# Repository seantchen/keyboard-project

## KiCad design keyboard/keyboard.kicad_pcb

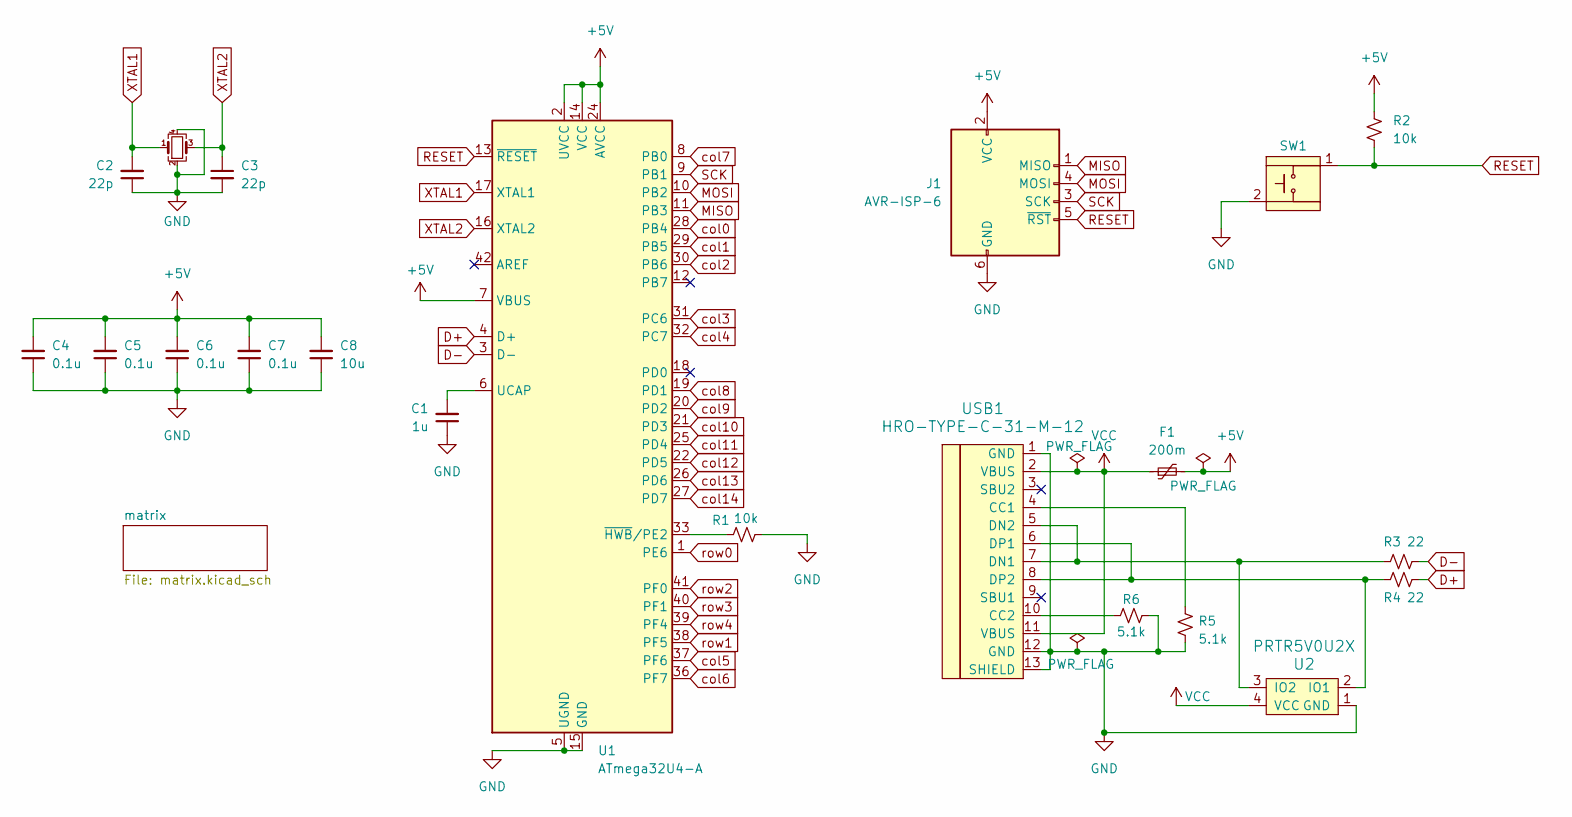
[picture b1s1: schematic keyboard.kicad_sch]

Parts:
C1: 1u; C_0805_2012Metric_Pad1.18x1.45mm_HandSolder
C2, C3: 22p; C_0805_2012Metric_Pad1.18x1.45mm_HandSolder
C4, C5, C6, C7: 0.1u; C_0805_2012Metric_Pad1.18x1.45mm_HandSolder
C8: 10u; C_0805_2012Metric_Pad1.18x1.45mm_HandSolder
F1: 200m; Fuse_1206_3216Metric_Pad1.42x1.75mm_HandSolder
J1: AVR-ISP-6; Reset_Pretty-Mask
R1, R2: 10k; R_0805_2012Metric_Pad1.20x1.40mm_HandSolder
R3, R4: 22; R_0805_2012Metric_Pad1.20x1.40mm_HandSolder
R5, R6: 5.1k; R_0805_2012Metric_Pad1.20x1.40mm_HandSolder
SW1: SW_SPST_SKQG_WithStem
U1: ATmega32U4-A; TQFP-44_10x10mm_P0.8mm
U2: PRTR5V0U2X; SOT143B
USB1: HRO-TYPE-C-31-M-12; HRO-TYPE-C-31-M-12-HandSoldering
Y1: Crystal_GND24_Small; Crystal_SMD_3225-4Pin_3.2x2.5mm_HandSoldering

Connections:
+5V: C4.2, C5.2, C6.2, C7.2, C8.2, F1.2, J1.2 (VCC), R2.1, U1.2 (UVCC), U1.7 (VBUS), U1.14 (VCC), U1.24 (AVCC), U1.34 (VCC), U1.44 (AVCC)
D+: R4.2, U1.4 (D+)
D-: R3.2, U1.3 (D-)
GND: C1.1, C2.1, C3.2, C4.1, C5.1, C6.1, C7.1, C8.1, J1.6 (GND), R1.2, R5.2, R6.2, SW1.2, U1.5 (UGND), U1.15 (GND), U1.23 (GND), U1.35 (GND), U1.43 (GND), U2.1 (GND), USB1.1 (GND), USB1.12 (GND), USB1.13 (SHIELD), Y1.2, Y1.4
MISO: J1.1 (MISO), U1.11 (PB3)
MOSI: J1.4 (MOSI), U1.10 (PB2)
unnamed: C1.2, U1.6 (UCAP)
unnamed: R1.1, U1.33 (~HWB/PE2)
unnamed: R4.1, U2.2 (IO1), USB1.6 (DP1), USB1.8 (DP2)
unnamed: R3.1, U2.3 (IO2), USB1.5 (DN2), USB1.7 (DN1)
unnamed: R5.1, USB1.4 (CC1)
unnamed: R6.1, USB1.10 (CC2)
RESET: J1.5 (~RST), R2.2, SW1.1, U1.13 (~RESET)
SCK: J1.3 (SCK), U1.9 (PB1)
VCC: F1.1, U2.4 (VCC), USB1.2 (VBUS), USB1.11 (VBUS)
XTAL1: C2.2, U1.17 (XTAL1), Y1.1
XTAL2: C3.1, U1.16 (XTAL2), Y1.3
col0: U1.28 (PB4); also elsewhere on the board
col1: U1.29 (PB5); also elsewhere on the board
col2: U1.30 (PB6); also elsewhere on the board
col3: U1.31 (PC6); also elsewhere on the board
col4: U1.32 (PC7); also elsewhere on the board
col5: U1.37 (PF6); also elsewhere on the board
col6: U1.36 (PF7); also elsewhere on the board
col7: U1.8 (PB0); also elsewhere on the board
col8: U1.19 (PD1); also elsewhere on the board
col9: U1.20 (PD2); also elsewhere on the board
col10: U1.21 (PD3); also elsewhere on the board
col11: U1.25 (PD4); also elsewhere on the board
col12: U1.22 (PD5); also elsewhere on the board
col13: U1.26 (PD6); also elsewhere on the board
col14: U1.27 (PD7); also elsewhere on the board
row0: U1.1 (PE6); also elsewhere on the board
row1: U1.38 (PF5); also elsewhere on the board
row2: U1.41 (PF0); also elsewhere on the board
row3: U1.40 (PF1); also elsewhere on the board
row4: U1.39 (PF4); also elsewhere on the board

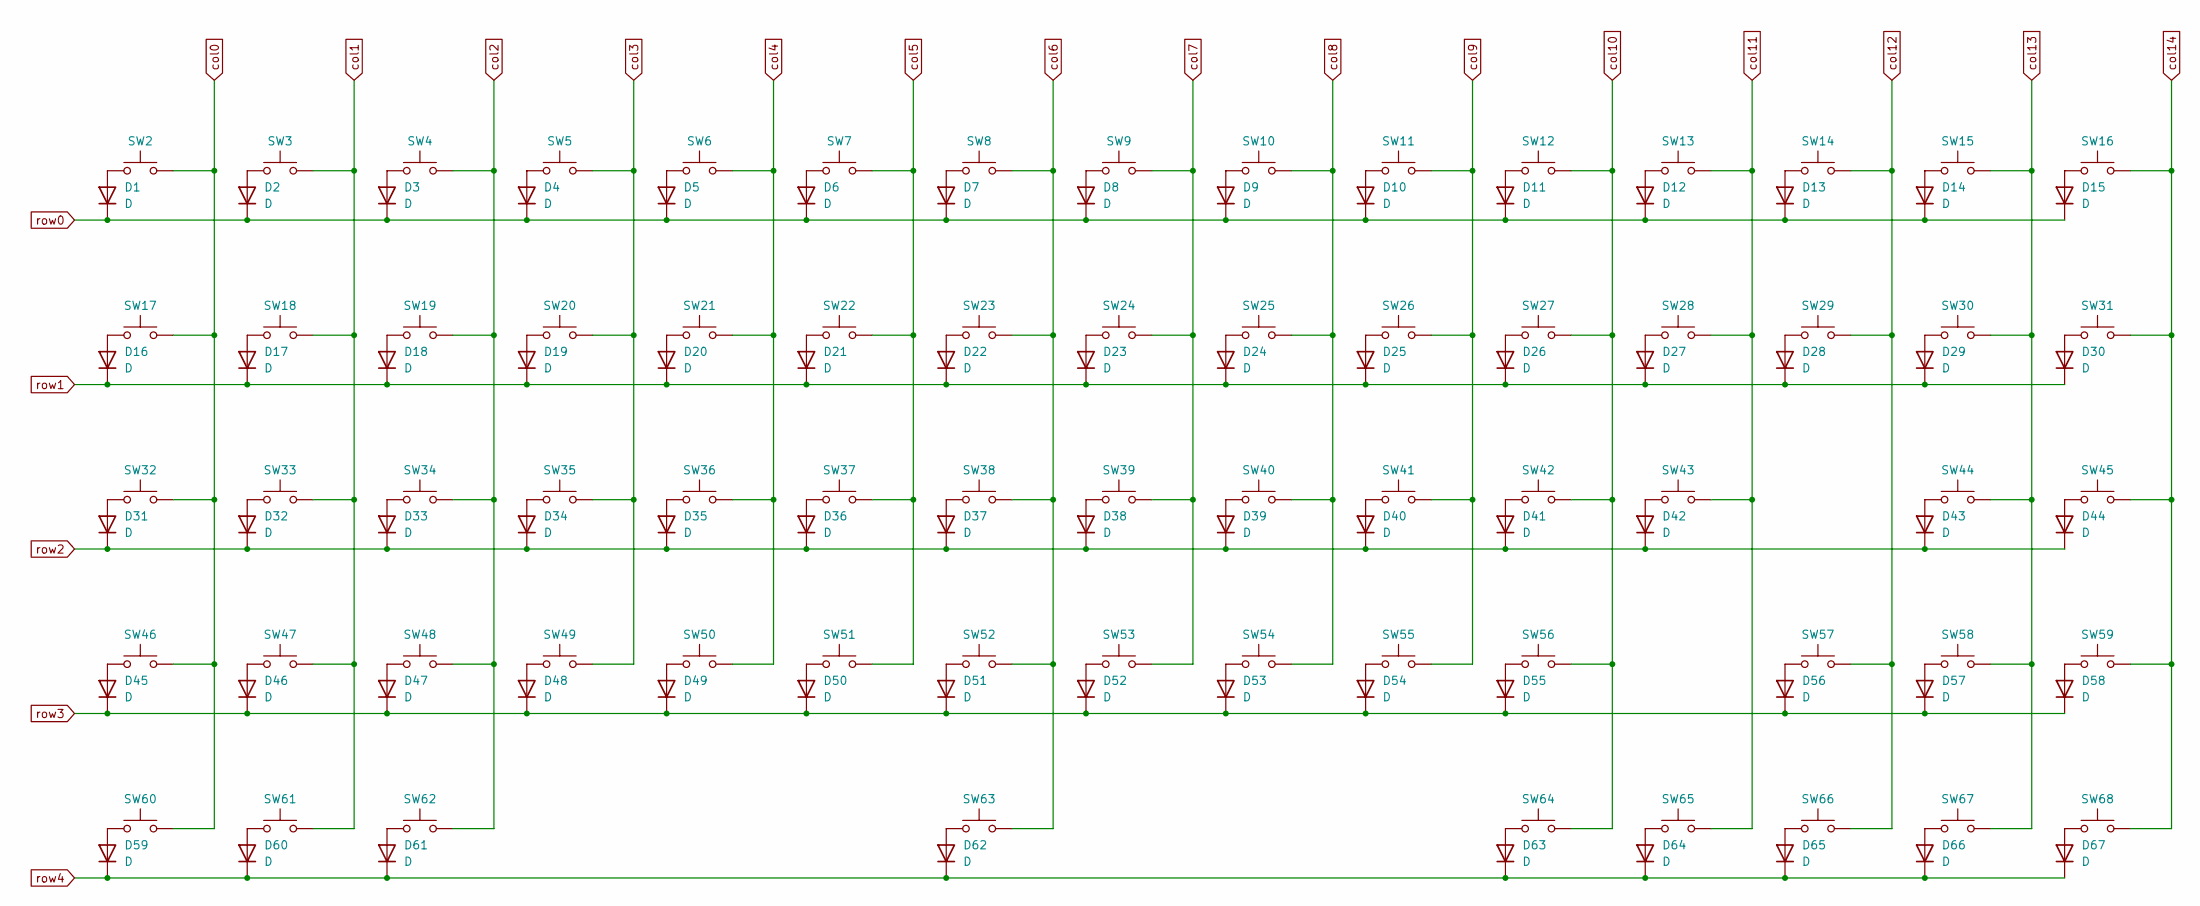
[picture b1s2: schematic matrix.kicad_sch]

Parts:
D1, D2, D3, D4, D5, D6, D7, D8, D9, D10, D11, D12, D13, D14, D15, D16, D17, D18, D19, D20, D21, D22, D23, D24, D25, D26, D27, D28, D29, D30, D31, D32, D33, D34, D35, D36, D37, D38, D39, D40, D41, D42, D43, D44, D45, D46, D47, D48, D49, D50, D51, D52, D53, D54, D55, D56, D57, D58, D59, D60, D61, D62, D63, D64, D65, D66, D67: D; D_SOD-123
SW2: ESC; MXOnly-1U-NoLED
SW3: 1; MXOnly-1U-NoLED
SW4: 2; MXOnly-1U-NoLED
SW5: 3; MXOnly-1U-NoLED
SW6: 4; MXOnly-1U-NoLED
SW7: 5; MXOnly-1U-NoLED
SW8: 6; MXOnly-1U-NoLED
SW9: 7; MXOnly-1U-NoLED
SW10: 8; MXOnly-1U-NoLED
SW11: 9; MXOnly-1U-NoLED
SW12: 0; MXOnly-1U-NoLED
SW13: -_; MXOnly-1U-NoLED
SW14: +=; MXOnly-1U-NoLED
SW15: BSPC; MXOnly-2U-NoLED
SW16: DEL; MXOnly-1U-NoLED
SW17: TAB; MXOnly-1.5U-NoLED
SW18: Q; MXOnly-1U-NoLED
SW19: W; MXOnly-1U-NoLED
SW20: E; MXOnly-1U-NoLED
SW21: R; MXOnly-1U-NoLED
SW22: T; MXOnly-1U-NoLED
SW23: Y; MXOnly-1U-NoLED
SW24: U; MXOnly-1U-NoLED
SW25: I; MXOnly-1U-NoLED
SW26: O; MXOnly-1U-NoLED
SW27: P; MXOnly-1U-NoLED
SW28: {[; MXOnly-1U-NoLED
SW29: }]; MXOnly-1U-NoLED
SW30: |\; MXOnly-1.5U-NoLED
SW31: PGUP; MXOnly-1U-NoLED
SW32: CAPS; MXOnly-1.75U-NoLED
SW33: A; MXOnly-1U-NoLED
SW34: S; MXOnly-1U-NoLED
SW35: D; MXOnly-1U-NoLED
SW36: F; MXOnly-1U-NoLED
SW37: G; MXOnly-1U-NoLED
SW38: H; MXOnly-1U-NoLED
SW39: J; MXOnly-1U-NoLED
SW40: K; MXOnly-1U-NoLED
SW41: L; MXOnly-1U-NoLED
SW42: :;; MXOnly-1U-NoLED
SW43: "'; MXOnly-1U-NoLED
SW44: ENTER; MXOnly-2.25U-NoLED
SW45: PGDN; MXOnly-1U-NoLED
SW46: SHIFT; MXOnly-2.25U-NoLED
SW47: Z; MXOnly-1U-NoLED
SW48: X; MXOnly-1U-NoLED
SW49: C; MXOnly-1U-NoLED
SW50: V; MXOnly-1U-NoLED
SW51: B; MXOnly-1U-NoLED
SW52: N; MXOnly-1U-NoLED
SW53: M; MXOnly-1U-NoLED
SW54: <,; MXOnly-1U-NoLED
SW55: >.; MXOnly-1U-NoLED
SW56: ?/; MXOnly-1U-NoLED
SW57: SHIFT; MXOnly-1.75U-NoLED
SW58: UP; MXOnly-1U-NoLED
SW59: END; MXOnly-1U-NoLED
SW60: CTRL; MXOnly-1.5U-NoLED
SW61: WIN; MXOnly-1.25U-NoLED
SW62: ALT; MXOnly-1.5U-NoLED
SW63: SPACE; MXOnly-6.25U-ReversedStabilizers-NoLED
SW64: FN; MXOnly-1.25U-NoLED
SW65: CTRL; MXOnly-1.25U-NoLED
SW66: LEFT; MXOnly-1U-NoLED
SW67: DOWN; MXOnly-1U-NoLED
SW68: RIGHT; MXOnly-1U-NoLED

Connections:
unnamed: D1.2 (A), SW2.1
unnamed: D2.2 (A), SW3.1
unnamed: D3.2 (A), SW4.1
unnamed: D4.2 (A), SW5.1
unnamed: D5.2 (A), SW6.1
unnamed: D6.2 (A), SW7.1
unnamed: D7.2 (A), SW8.1
unnamed: D8.2 (A), SW9.1
unnamed: D9.2 (A), SW10.1
unnamed: D10.2 (A), SW11.1
unnamed: D11.2 (A), SW12.1
unnamed: D12.2 (A), SW13.1
unnamed: D13.2 (A), SW14.1
unnamed: D14.2 (A), SW15.1
unnamed: D15.2 (A), SW16.1
unnamed: D16.2 (A), SW17.1
unnamed: D17.2 (A), SW18.1
unnamed: D18.2 (A), SW19.1
unnamed: D19.2 (A), SW20.1
unnamed: D20.2 (A), SW21.1
unnamed: D21.2 (A), SW22.1
unnamed: D22.2 (A), SW23.1
unnamed: D23.2 (A), SW24.1
unnamed: D24.2 (A), SW25.1
unnamed: D25.2 (A), SW26.1
unnamed: D26.2 (A), SW27.1
unnamed: D27.2 (A), SW28.1
unnamed: D28.2 (A), SW29.1
unnamed: D29.2 (A), SW30.1
unnamed: D30.2 (A), SW31.1
unnamed: D31.2 (A), SW32.1
unnamed: D32.2 (A), SW33.1
unnamed: D33.2 (A), SW34.1
unnamed: D34.2 (A), SW35.1
unnamed: D35.2 (A), SW36.1
unnamed: D36.2 (A), SW37.1
unnamed: D37.2 (A), SW38.1
unnamed: D38.2 (A), SW39.1
unnamed: D39.2 (A), SW40.1
unnamed: D40.2 (A), SW41.1
unnamed: D41.2 (A), SW42.1
unnamed: D42.2 (A), SW43.1
unnamed: D43.2 (A), SW44.1
unnamed: D44.2 (A), SW45.1
unnamed: D45.2 (A), SW46.1
unnamed: D46.2 (A), SW47.1
unnamed: D47.2 (A), SW48.1
unnamed: D48.2 (A), SW49.1
unnamed: D49.2 (A), SW50.1
unnamed: D50.2 (A), SW51.1
unnamed: D51.2 (A), SW52.1
unnamed: D52.2 (A), SW53.1
unnamed: D53.2 (A), SW54.1
unnamed: D54.2 (A), SW55.1
unnamed: D55.2 (A), SW56.1
unnamed: D56.2 (A), SW57.1
unnamed: D57.2 (A), SW58.1
unnamed: D58.2 (A), SW59.1
unnamed: D59.2 (A), SW60.1
unnamed: D60.2 (A), SW61.1
unnamed: D61.2 (A), SW62.1
unnamed: D62.2 (A), SW63.1
unnamed: D63.2 (A), SW64.1
unnamed: D64.2 (A), SW65.1
unnamed: D65.2 (A), SW66.1
unnamed: D66.2 (A), SW67.1
unnamed: D67.2 (A), SW68.1
col0: SW2.2, SW17.2, SW32.2, SW46.2, SW60.2; also elsewhere on the board
col1: SW3.2, SW18.2, SW33.2, SW47.2, SW61.2; also elsewhere on the board
col2: SW4.2, SW19.2, SW34.2, SW48.2, SW62.2; also elsewhere on the board
col3: SW5.2, SW20.2, SW35.2, SW49.2; also elsewhere on the board
col4: SW6.2, SW21.2, SW36.2, SW50.2; also elsewhere on the board
col5: SW7.2, SW22.2, SW37.2, SW51.2; also elsewhere on the board
col6: SW8.2, SW23.2, SW38.2, SW52.2, SW63.2; also elsewhere on the board
col7: SW9.2, SW24.2, SW39.2, SW53.2; also elsewhere on the board
col8: SW10.2, SW25.2, SW40.2, SW54.2; also elsewhere on the board
col9: SW11.2, SW26.2, SW41.2, SW55.2; also elsewhere on the board
col10: SW12.2, SW27.2, SW42.2, SW56.2, SW64.2; also elsewhere on the board
col11: SW13.2, SW28.2, SW43.2, SW65.2; also elsewhere on the board
col12: SW14.2, SW29.2, SW57.2, SW66.2; also elsewhere on the board
col13: SW15.2, SW30.2, SW44.2, SW58.2, SW67.2; also elsewhere on the board
col14: SW16.2, SW31.2, SW45.2, SW59.2, SW68.2; also elsewhere on the board
row0: D1.1 (K), D2.1 (K), D3.1 (K), D4.1 (K), D5.1 (K), D6.1 (K), D7.1 (K), D8.1 (K), D9.1 (K), D10.1 (K), D11.1 (K), D12.1 (K), D13.1 (K), D14.1 (K), D15.1 (K); also elsewhere on the board
row1: D16.1 (K), D17.1 (K), D18.1 (K), D19.1 (K), D20.1 (K), D21.1 (K), D22.1 (K), D23.1 (K), D24.1 (K), D25.1 (K), D26.1 (K), D27.1 (K), D28.1 (K), D29.1 (K), D30.1 (K); also elsewhere on the board
row2: D31.1 (K), D32.1 (K), D33.1 (K), D34.1 (K), D35.1 (K), D36.1 (K), D37.1 (K), D38.1 (K), D39.1 (K), D40.1 (K), D41.1 (K), D42.1 (K), D43.1 (K), D44.1 (K); also elsewhere on the board
row3: D45.1 (K), D46.1 (K), D47.1 (K), D48.1 (K), D49.1 (K), D50.1 (K), D51.1 (K), D52.1 (K), D53.1 (K), D54.1 (K), D55.1 (K), D56.1 (K), D57.1 (K), D58.1 (K); also elsewhere on the board
row4: D59.1 (K), D60.1 (K), D61.1 (K), D62.1 (K), D63.1 (K), D64.1 (K), D65.1 (K), D66.1 (K), D67.1 (K); also elsewhere on the board

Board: 2 copper layers, 155 parts (88 on the bottom side), 104 nets, no tracks yet.

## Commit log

2025-12-31 Added KiCad libaries
2026-01-02 Created project folder and added symbols + footprints
2026-01-05 Finished electronic schema of MCU
2026-01-05 Finished electronic schema of matrix
2026-01-07 Assigned footprints + fixed errors
2026-01-11 Finished keyboard switch layout for PCB
2026-01-13 Finished diode layout and changed switch footprints to no-LED
2026-02-15 Crudely arranged USB-C and MCU footprints and cut PCB edges.
